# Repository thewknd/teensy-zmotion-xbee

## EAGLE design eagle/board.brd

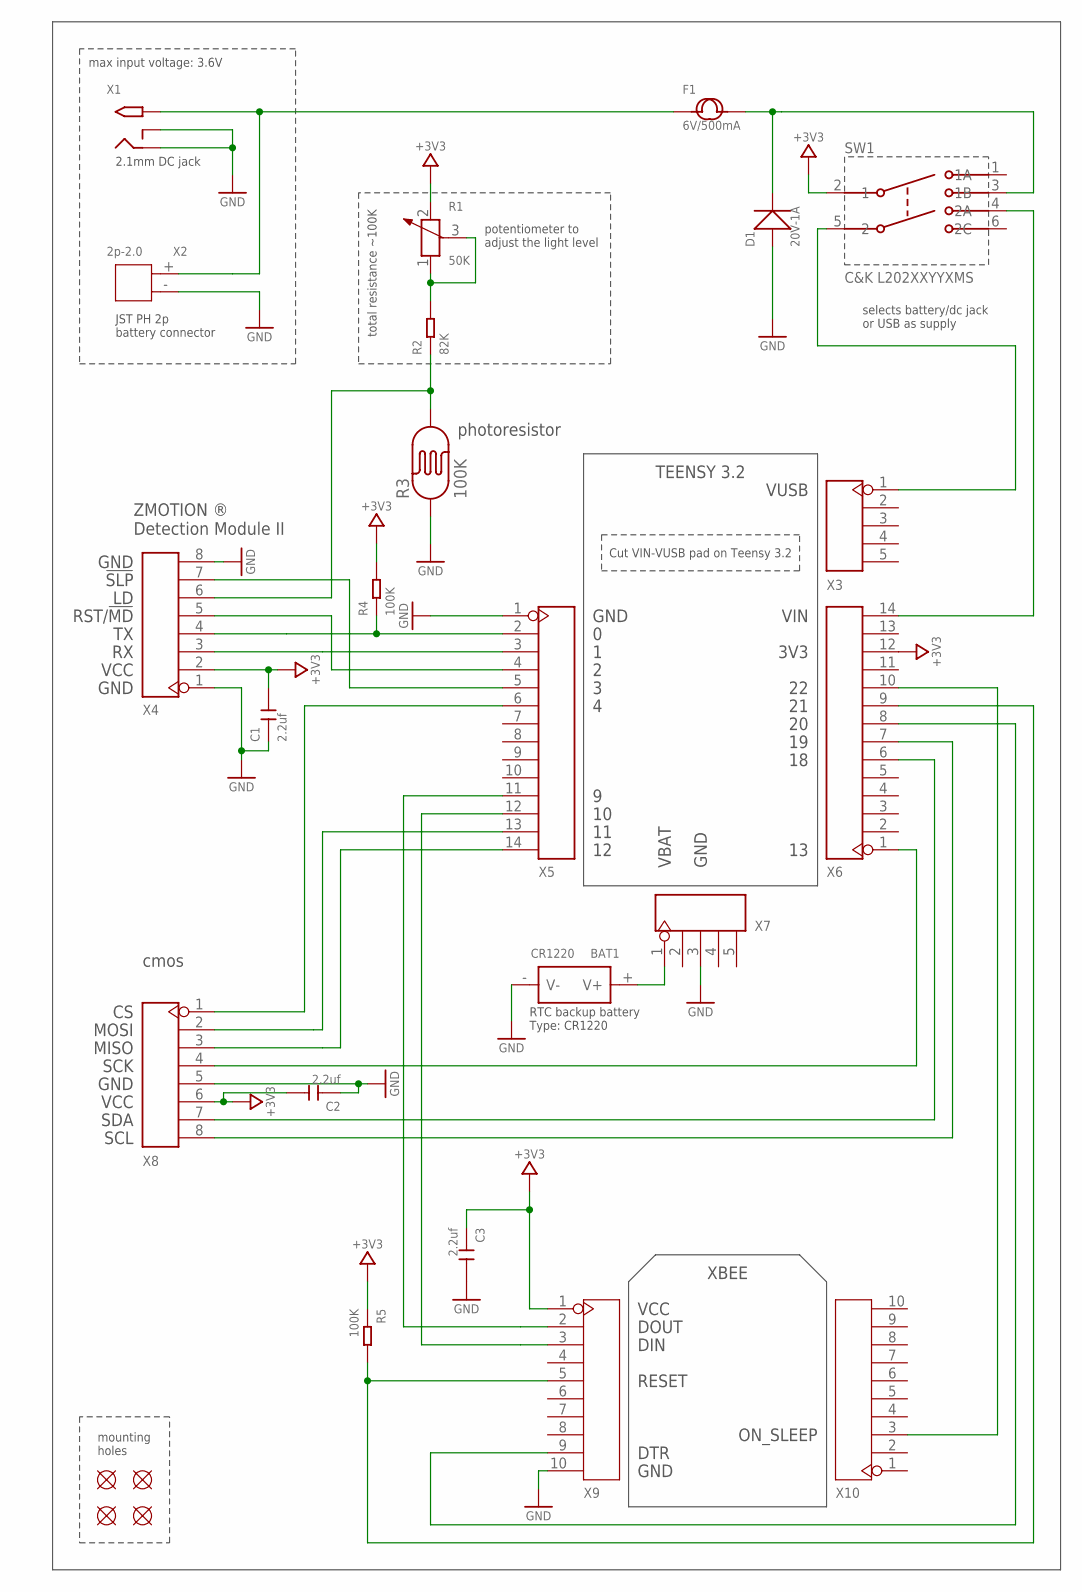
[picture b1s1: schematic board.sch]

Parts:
BAT1: CR1220; BAT2P-SMD-16.4-CR1220
C1, C2, C3: 2.2uf; C0805
D1: 20V-1A; SOD-123
F1: 6V/500mA; F1206
MNT1, MNT2, MNT3, MNT4: MOUNTING_HOLE3.2MM_SILK; HOLE_3.2MM_SILK
R1: 50K; ADJR3-7.0X7.0X5.0MM
R2: 82K; R0805
R3: 100K; CDS_4.2X3.4MM_PITCH:2.54MM
R4, R5: 100K; R0805
SW1: C&K L202XXYYXMS; C&K_L102_MS
X1: 2.1MMJACKTHM; PJ-102A
X2: 2p-2.0; H2-2.0-6X4.5MM
X3, X7: 5p-2.54; H5-2.54
X4, X8: 8p-2.54; H8-2.54
X5, X6: 14p-2.54; H14-2.54
X9, X10: 10p-2.0; H10-2.0

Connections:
+3V3: C1.2, C2.2, C3.1, R1.2 (3), R4.2, R5.1, SW1.2 (1), X4.2, X6.12, X8.6, X9.1
D3: X4.7, X5.5
GND: BAT1.- (V-), C1.1, C2.1, C3.2, D1.+, R3.P$1, X1.RING, X1.RING_SW, X2.-, X4.1, X4.8, X5.1, X7.3, X8.5, X9.10
unnamed: X5.11, X9.2
unnamed: X5.12, X9.3
unnamed: BAT1.+ (V+), X7.1
unnamed: X4.3, X5.3
unnamed: R4.1, X4.4, X5.2
unnamed: X4.5, X5.4
unnamed: R1.1, R1.3 (2), R2.2
unnamed: X6.7, X8.8
unnamed: X6.6, X8.7
unnamed: X6.1, X8.4
unnamed: X5.14, X8.3
unnamed: X5.13, X8.2
unnamed: X5.6, X8.1
unnamed: R2.1, R3.P$2, X4.6
unnamed: X6.8, X9.9
unnamed: R5.2, X6.9, X9.5
unnamed: X6.10, X10.3
unnamed: SW1.4 (2A), X6.14
unnamed: SW1.5 (2), X3.1
unnamed: D1.-, F1.2, SW1.3 (1B)
unnamed: F1.1, X1.TIP, X2.+

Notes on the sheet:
ZMOTION ® Detection Module II
cmos
photoresistor
ON_SLEEP
GND
DTR
RESET
DIN
DOUT
VCC
XBEE
potentiometer to adjust the light level
total resistance ~100K
JST PH 2p battery connector
2.1mm DC jack
max input voltage: 3.6V
selects battery/dc jack or USB as supply
RTC backup battery Type: CR1220
3V3
VIN
VUSB
VBAT
TEENSY 3.2
mounting holes
RST/!MD
!SLP
SCL
SDA
SCK
MISO
MOSI
Cut VIN-VUSB pad on Teensy 3.2

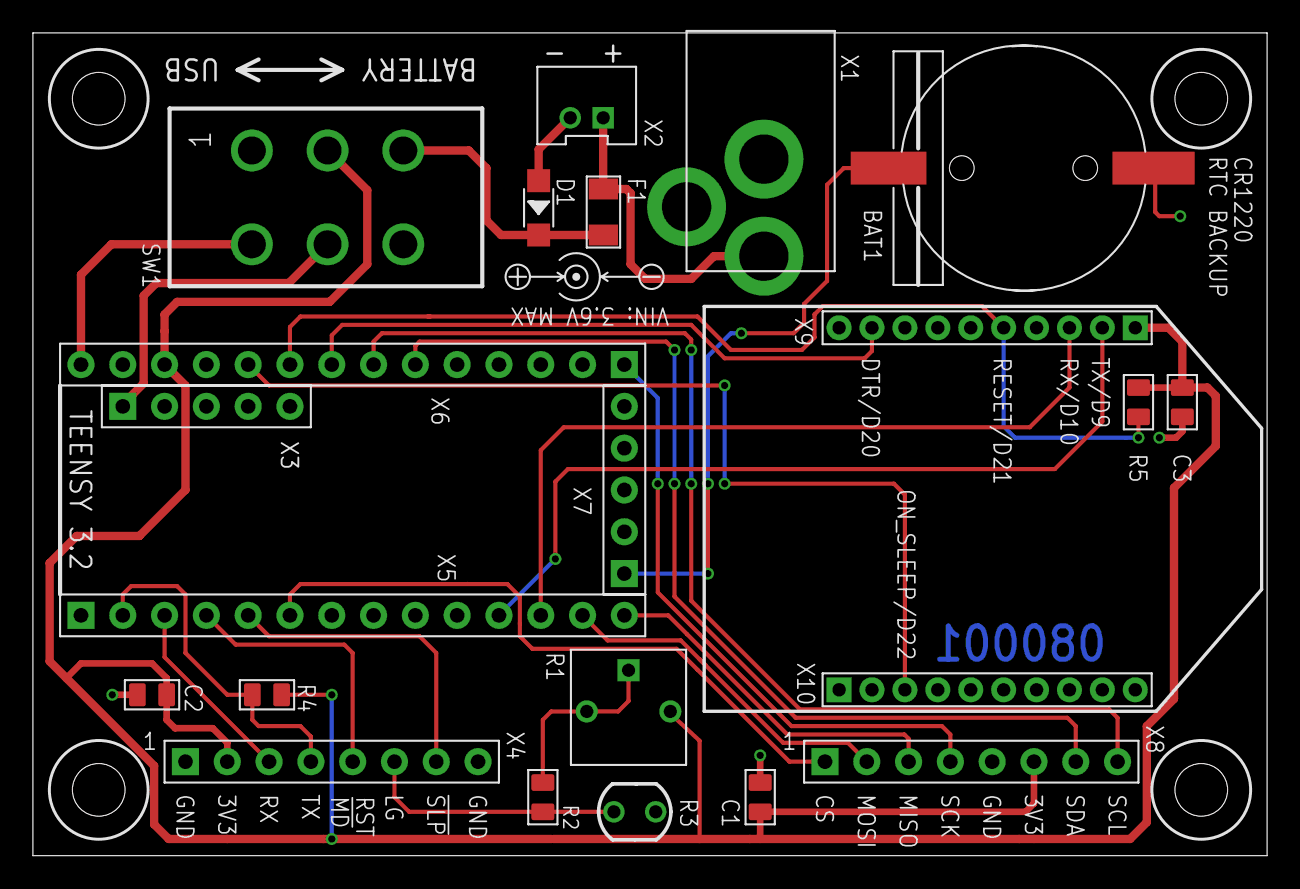
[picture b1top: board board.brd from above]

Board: 2 copper layers, 75.0 x 50.0 mm, 27 parts (0 on the bottom side), 24 nets.

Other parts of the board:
U$1: DCBARREL_DESC

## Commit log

2015-12-04 first
2015-12-04 new bom.csv
2015-12-05 new slide switch new capacitors
2015-12-05 add pcb number
2015-12-05 fix trace width
2015-12-05 fix SLK silkscreen
2015-12-06 fix silkscreen for pin 4
